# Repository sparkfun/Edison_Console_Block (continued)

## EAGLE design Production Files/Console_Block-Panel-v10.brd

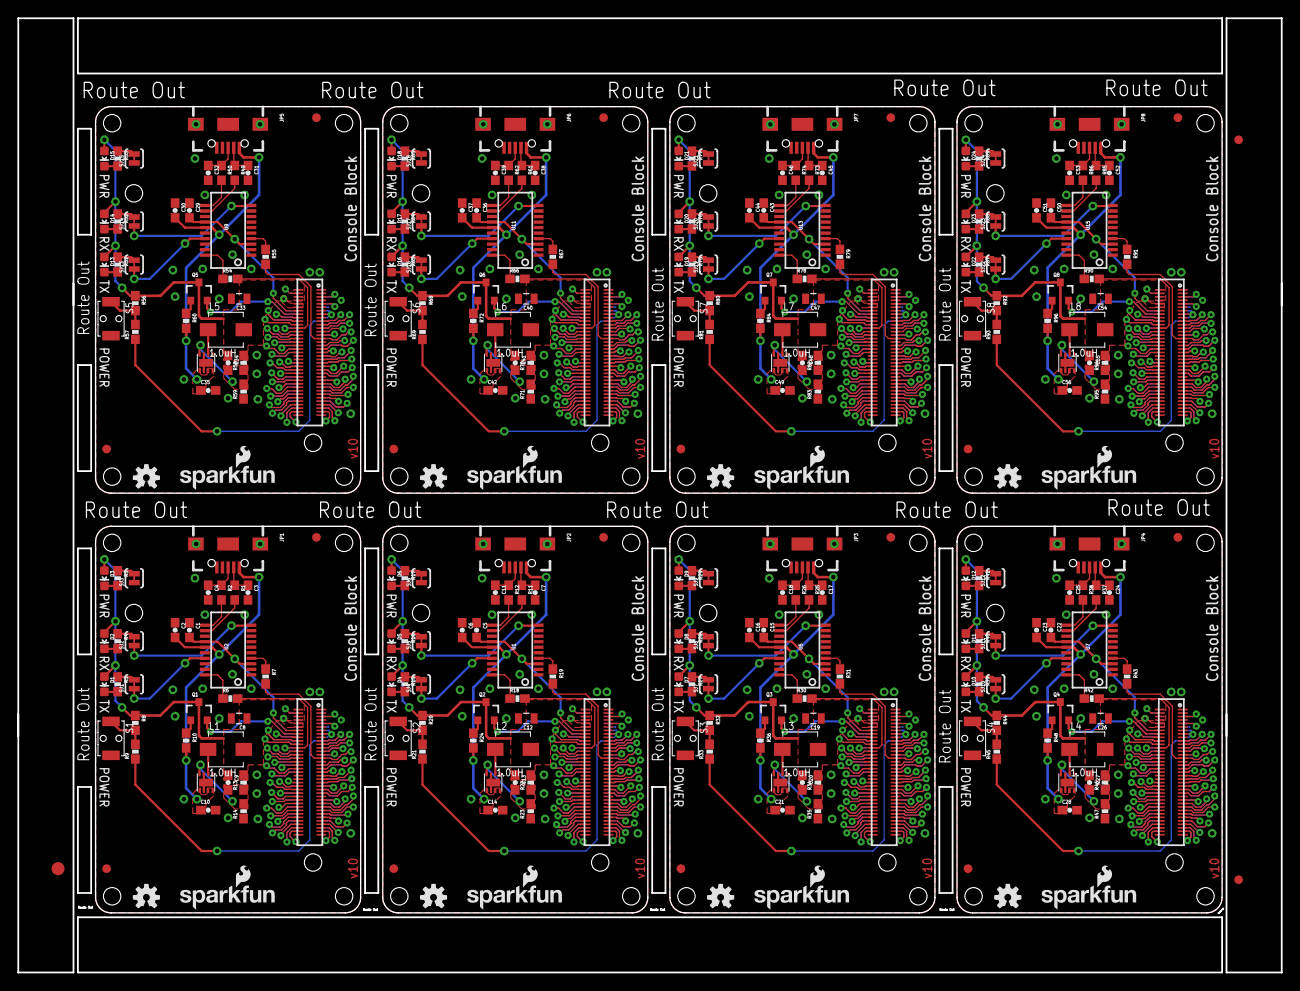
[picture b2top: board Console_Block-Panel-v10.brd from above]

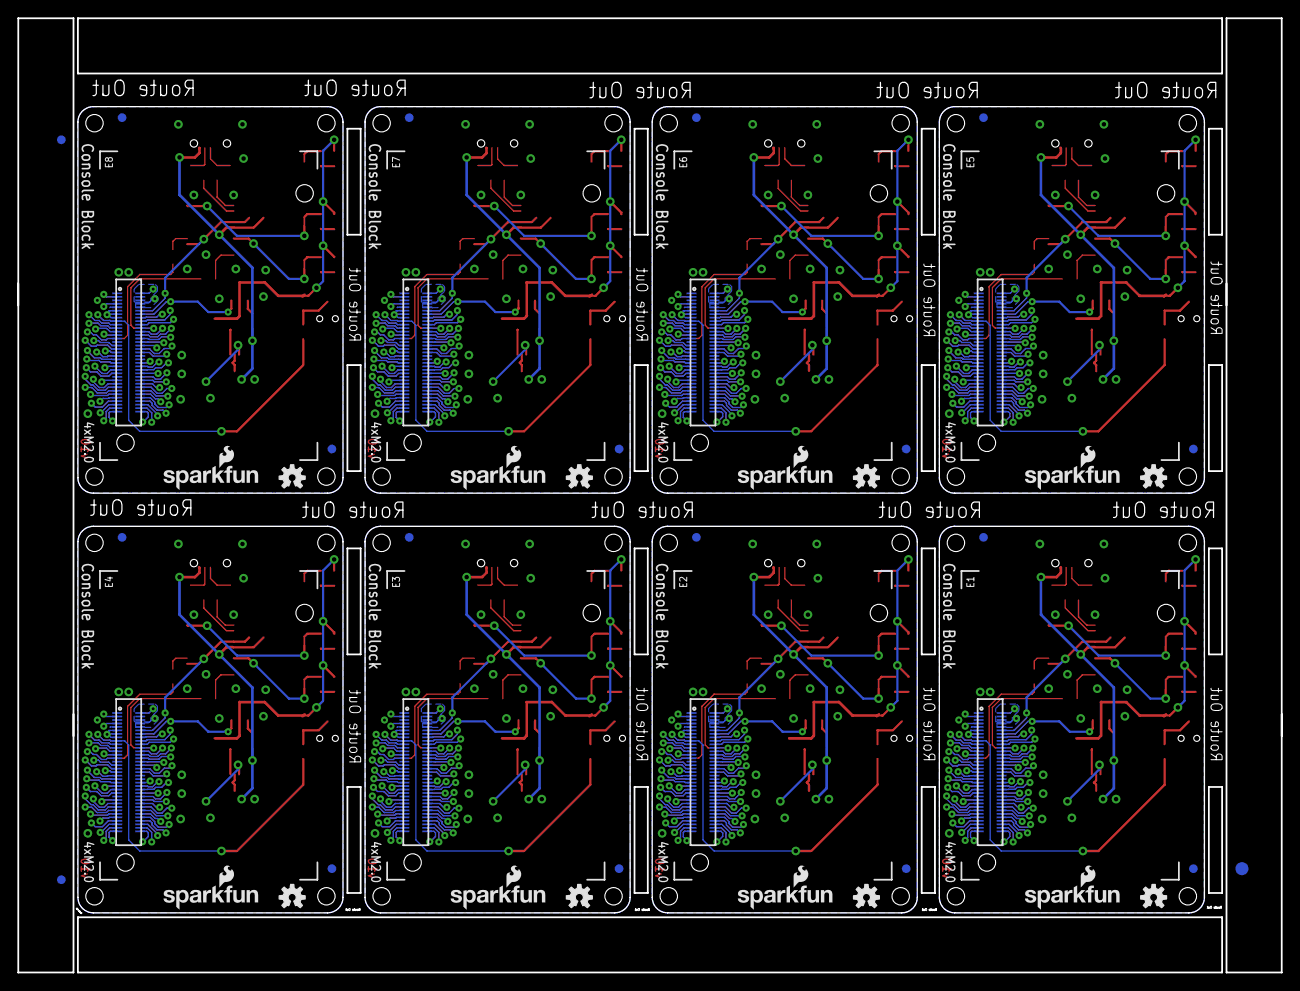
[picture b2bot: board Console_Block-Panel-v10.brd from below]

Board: 2 copper layers, 145.3 x 109.7 mm, 334 parts (51 on the bottom side), 616 nets.

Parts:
C1, C2, C5, C6, C15, C16, C22, C23, C29, C30, C36, C37, C43, C44, C50, C51: 0.1uF; 0603-CAP
C3, C4, C7, C9, C11, C13, C17, C18, C20, C24, C25, C27, C31, C32, C34, C38, C39, C41, C45, C46, C48, C52, C53, C55: 47pF; 0603-CAP
C8, C12, C19, C26, C33, C40, C47, C54: 22uF; 0805
C10, C14, C21, C28, C35, C42, C49, C56: 4.7uF; 0603-CAP
D1, D4, D7, D10, D13, D16, D19, D22: RED; LED-0603
D2, D5, D8, D11, D14, D17, D20, D23: YELLOW; LED-0603
D3, D6, D9, D12, D15, D18, D21, D24: BLUE; LED-0603
E1, E2, E3, E4, E5, E6, E7, E8: EDISON_CONNECTOR_FULLMOUNTING_HOLES; EDISON_DAUGHTER
E$1, E$2: FIDUCIAL-1.5X3
E$3, E$4, E$5, E$6: FIDUCIAL-1X2
FID1, FID2, FID3, FID4, FID5, FID6, FID7, FID8, FID9, FID10, FID11, FID12, FID13, FID14, FID15, FID16, FID17, FID18, FID19, FID20, FID21, FID22, FID23, FID24, FID25, FID26, FID27, FID28, FID29, FID30, FID31, FID32: FIDUCIAL1X2; FIDUCIAL-1X2
JP1, JP2, JP3, JP4, JP5, JP6, JP7, JP8: USB_MICROB; USB-B-MICRO-SMD_V03
L1, L2, L3, L4, L5, L6, L7, L8: 1.0uH; INDUCTOR-SRP4020
LOGO1, LOGO3, LOGO6, LOGO7, LOGO10, LOGO11, LOGO14, LOGO15, LOGO18, LOGO19, LOGO22, LOGO23, LOGO26, LOGO27, LOGO30, LOGO31: SFE_LOGO_NAME_FLAME.1_INCH; SFE_LOGO_NAME_FLAME_.1
LOGO2, LOGO4, LOGO5, LOGO8, LOGO9, LOGO12, LOGO13, LOGO16, LOGO17, LOGO20, LOGO21, LOGO24, LOGO25, LOGO28, LOGO29, LOGO32: OSHW-LOGOS; OSHW-LOGO-S
Q1, Q2, Q3, Q4, Q5, Q6, Q7, Q8: BSS138; SOT23-3
R1, R2, R11, R12, R25, R26, R37, R38, R49, R50, R61, R62, R73, R74, R85, R86: 27; 0603
R3, R4, R5, R10, R15, R16, R17, R24, R27, R28, R29, R36, R39, R40, R41, R48, R51, R52, R53, R60, R63, R64, R65, R72, R75, R76, R77, R84, R87, R88, R89, R96: 1K; 0603-RES
R6, R7, R18, R19, R30, R31, R42, R43, R54, R55, R66, R67, R78, R79, R90, R91: 100; 0603-RES
R8, R20, R32, R44, R56, R68, R80, R92: 10K; 0603-RES
R9, R21, R33, R45, R57, R69, R81, R93: 22; 0603-RES
R13, R22, R34, R46, R58, R70, R82, R94: 680k; 0603-RES
R14, R23, R35, R47, R59, R71, R83, R95: 120k; 0603-RES
S1, S2, S3, S4, S5, S6, S7, S8: POWER; TACTILE_SWITCH-SMD-RIGHT-ANGLE
SJ1, SJ2, SJ3, SJ4, SJ5, SJ6, SJ7, SJ8, SJ9, SJ10, SJ11, SJ12, SJ13, SJ14, SJ15, SJ16, SJ17, SJ18, SJ19, SJ20, SJ21, SJ22, SJ23, SJ24: JUMPER-PAD-2-NC_BY_TRACE; PAD-JUMPER-2-NC_BY_TRACE_YES_SILK
U1, U2, U5, U7, U9, U11, U13, U15: FT231XS-U; SSOP20_L
U3, U4, U6, U8, U10, U12, U14, U16: TPS62065; WSON-8-PAD
U$1, U$2, U$3, U$4, U$5, U$6, U$7, U$8: EDISON_CONNECTOR_FULLHEADER; DF40C-70DP-0.4(51)

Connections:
1.8V: C1.2, E1.12, U2.3, U2.14, U$3.12
1.8V1: C5.2, E2.12, U1.3, U1.14, U$1.12
1.8V2: C15.2, E3.12, U5.3, U5.14, U$2.12
1.8V3: C22.2, E4.12, U7.3, U7.14, U$4.12
1.8V4: C29.2, E5.12, U9.3, U9.14, U$5.12
1.8V5: C36.2, E6.12, U11.3, U11.14, U$6.12
1.8V6: C43.2, E7.12, U13.3, U13.14, U$7.12
1.8V7: C50.2, E8.12, U15.3, U15.14, U$8.12
3.3V: E1.8, E1.10, U$3.8, U$3.10
3.3V1: E2.8, E2.10, U$1.8, U$1.10
3.3V2: E3.8, E3.10, U$2.8, U$2.10
3.3V3: E4.8, E4.10, U$4.8, U$4.10
3.3V4: E5.8, E5.10, U$5.8, U$5.10
3.3V5: E6.8, E6.10, U$6.8, U$6.10
3.3V6: E7.8, E7.10, U$7.8, U$7.10
3.3V7: E8.8, E8.10, U$8.8, U$8.10
5V: C2.2, C10.1, JP1.VBUS1, R10.2, U2.15, U4.5, U4.7, U4.8
5V1: C6.2, C14.1, JP2.VBUS1, R24.2, U1.15, U3.5, U3.7, U3.8
5V2: C16.2, C21.1, JP3.VBUS1, R36.2, U5.15, U6.5, U6.7, U6.8
5V3: C23.2, C28.1, JP4.VBUS1, R48.2, U7.15, U8.5, U8.7, U8.8
5V4: C30.2, C35.1, JP5.VBUS1, R60.2, U9.15, U10.5, U10.7, U10.8
5V5: C37.2, C42.1, JP6.VBUS1, R72.2, U11.15, U12.5, U12.7, U12.8
5V6: C44.2, C49.1, JP7.VBUS1, R84.2, U13.15, U14.5, U14.7, U14.8
5V7: C51.2, C56.1, JP8.VBUS1, R96.2, U15.15, U16.5, U16.7, U16.8
DCIN: E1.14, Q1.2, U$3.14
DCIN1: E2.14, Q2.2, U$1.14
DCIN2: E3.14, Q3.2, U$2.14
DCIN3: E4.14, Q4.2, U$4.14
DCIN4: E5.14, Q5.2, U$5.14
DCIN5: E6.14, Q6.2, U$6.14
DCIN6: E7.14, Q7.2, U$7.14
DCIN7: E8.14, Q8.2, U$8.14
FAULT: E1.19, U$3.19
FAULT1: E2.19, U$1.19
FAULT2: E3.19, U$2.19
FAULT3: E4.19, U$4.19
FAULT4: E5.19, U$5.19
FAULT5: E6.19, U$6.19
FAULT6: E7.19, U$7.19
FAULT7: E8.19, U$8.19
FW_RCVR: E1.69, U$3.69
FW_RCVR1: E2.69, U$1.69
FW_RCVR2: E3.69, U$2.69
FW_RCVR3: E4.69, U$4.69
FW_RCVR4: E5.69, U$5.69
FW_RCVR5: E6.69, U$6.69
FW_RCVR6: E7.69, U$7.69
FW_RCVR7: E8.69, U$8.69
GND: C1.1, C2.1, C3.2, C4.2, C8.2, C10.2, E1.1, E1.5, E1.9, E1.11, E1.13, E1.15, JP1.GND1, JP1.SHIELD1, JP1.SHIELD2, JP1.SHIELD3, R14.1, S1.2, SJ3.1, U2.6, U2.16, U4.1, U4.3, U4.6, U4.PAD, U$3.1, U$3.5, U$3.9, U$3.11, U$3.13, U$3.15
GND1: C5.1, C6.1, C7.2, C11.2, C12.2, C14.2, E2.1, E2.5, E2.9, E2.11, E2.13, E2.15, JP2.GND1, JP2.SHIELD1, JP2.SHIELD2, JP2.SHIELD3, R23.1, S2.2, SJ6.1, U1.6, U1.16, U3.1, U3.3, U3.6, U3.PAD, U$1.1, U$1.5, U$1.9, U$1.11, U$1.13, U$1.15
GND2: C15.1, C16.1, C17.2, C18.2, C19.2, C21.2, E3.1, E3.5, E3.9, E3.11, E3.13, E3.15, JP3.GND1, JP3.SHIELD1, JP3.SHIELD2, JP3.SHIELD3, R35.1, S3.2, SJ9.1, U5.6, U5.16, U6.1, U6.3, U6.6, U6.PAD, U$2.1, U$2.5, U$2.9, U$2.11, U$2.13, U$2.15
GND3: C22.1, C23.1, C24.2, C25.2, C26.2, C28.2, E4.1, E4.5, E4.9, E4.11, E4.13, E4.15, JP4.GND1, JP4.SHIELD1, JP4.SHIELD2, JP4.SHIELD3, R47.1, S4.2, SJ12.1, U7.6, U7.16, U8.1, U8.3, U8.6, U8.PAD, U$4.1, U$4.5, U$4.9, U$4.11, U$4.13, U$4.15
GND4: C29.1, C30.1, C31.2, C32.2, C33.2, C35.2, E5.1, E5.5, E5.9, E5.11, E5.13, E5.15, JP5.GND1, JP5.SHIELD1, JP5.SHIELD2, JP5.SHIELD3, R59.1, S5.2, SJ15.1, U9.6, U9.16, U10.1, U10.3, U10.6, U10.PAD, U$5.1, U$5.5, U$5.9, U$5.11, U$5.13, U$5.15
GND5: C36.1, C37.1, C38.2, C39.2, C40.2, C42.2, E6.1, E6.5, E6.9, E6.11, E6.13, E6.15, JP6.GND1, JP6.SHIELD1, JP6.SHIELD2, JP6.SHIELD3, R71.1, S6.2, SJ18.1, U11.6, U11.16, U12.1, U12.3, U12.6, U12.PAD, U$6.1, U$6.5, U$6.9, U$6.11, U$6.13, U$6.15
GND6: C43.1, C44.1, C45.2, C46.2, C47.2, C49.2, E7.1, E7.5, E7.9, E7.11, E7.13, E7.15, JP7.GND1, JP7.SHIELD1, JP7.SHIELD2, JP7.SHIELD3, R83.1, S7.2, SJ21.1, U13.6, U13.16, U14.1, U14.3, U14.6, U14.PAD, U$7.1, U$7.5, U$7.9, U$7.11, U$7.13, U$7.15
GND7: C50.1, C51.1, C52.2, C53.2, C54.2, C56.2, E8.1, E8.5, E8.9, E8.11, E8.13, E8.15, JP8.GND1, JP8.SHIELD1, JP8.SHIELD2, JP8.SHIELD3, R95.1, S8.2, SJ24.1, U15.6, U15.16, U16.1, U16.3, U16.6, U16.PAD, U$8.1, U$8.5, U$8.9, U$8.11, U$8.13, U$8.15
GP1: E2.48, U$1.48
GP2: E2.42, U$1.42
GP3: E2.34, U$1.34
GP4: E2.32, U$1.32
GP5: E2.30, U$1.30
GP6: E2.28, U$1.28
GP7: E2.26, U$1.26
GP8: E2.25, U$1.25
GP9: E2.24, U$1.24
GP10: E3.48, U$2.48
GP11: E3.42, U$2.42
GP12: E3.34, U$2.34
GP12_PWM0: E1.35, U$3.35
GP12_PWM1: E2.35, U$1.35
GP12_PWM2: E3.35, U$2.35
GP12_PWM3: E4.35, U$4.35
GP12_PWM4: E5.35, U$5.35
GP12_PWM5: E6.35, U$6.35
GP12_PWM6: E7.35, U$7.35
GP12_PWM7: E8.35, U$8.35
GP13: E3.32, U$2.32
GP13_PWM1: E1.33, U$3.33
GP13_PWM2: E2.33, U$1.33
GP13_PWM3: E3.33, U$2.33
GP13_PWM4: E4.33, U$4.33
GP13_PWM5: E5.33, U$5.33
GP13_PWM6: E6.33, U$6.33
GP13_PWM7: E7.33, U$7.33
GP13_PWM8: E8.33, U$8.33
GP14: E1.48, U$3.48
GP15: E1.42, U$3.42
GP16: E3.30, U$2.30
GP17: E3.28, U$2.28
GP18: E3.26, U$2.26
GP19: E3.25, U$2.25
GP19_I2C_1_SCL: E1.41, U$3.41
GP19_I2C_1_SCL1: E2.41, U$1.41
GP19_I2C_1_SCL2: E3.41, U$2.41
GP19_I2C_1_SCL3: E4.41, U$4.41
GP19_I2C_1_SCL4: E5.41, U$5.41
GP19_I2C_1_SCL5: E6.41, U$6.41
GP19_I2C_1_SCL6: E7.41, U$7.41
GP19_I2C_1_SCL7: E8.41, U$8.41
GP20: E3.24, U$2.24
GP20_I2C_1_SDA: E1.43, U$3.43
GP20_I2C_1_SDA1: E2.43, U$1.43
GP20_I2C_1_SDA2: E3.43, U$2.43
GP20_I2C_1_SDA3: E4.43, U$4.43
GP20_I2C_1_SDA4: E5.43, U$5.43
GP20_I2C_1_SDA5: E6.43, U$6.43
GP20_I2C_1_SDA6: E7.43, U$7.43
GP20_I2C_1_SDA7: E8.43, U$8.43
GP21: E4.48, U$4.48
GP22: E4.42, U$4.42
GP23: E4.34, U$4.34
GP24: E4.32, U$4.32
GP25: E4.30, U$4.30
GP26: E4.28, U$4.28
GP27: E4.26, U$4.26
GP27_I2C_6_SCL: E1.45, U$3.45
GP27_I2C_6_SCL1: E2.45, U$1.45
GP27_I2C_6_SCL2: E3.45, U$2.45
GP27_I2C_6_SCL3: E4.45, U$4.45
GP27_I2C_6_SCL4: E5.45, U$5.45
GP27_I2C_6_SCL5: E6.45, U$6.45
GP27_I2C_6_SCL6: E7.45, U$7.45
GP27_I2C_6_SCL7: E8.45, U$8.45
GP28: E4.25, U$4.25
GP28_I2C_6_SDA: E1.47, U$3.47
GP28_I2C_6_SDA1: E2.47, U$1.47
GP28_I2C_6_SDA2: E3.47, U$2.47
GP28_I2C_6_SDA3: E4.47, U$4.47
GP28_I2C_6_SDA4: E5.47, U$5.47
GP28_I2C_6_SDA5: E6.47, U$6.47
GP28_I2C_6_SDA6: E7.47, U$7.47
GP28_I2C_6_SDA7: E8.47, U$8.47
GP29: E4.24, U$4.24
GP30: E5.48, U$5.48
GP31: E5.42, U$5.42
GP32: E5.34, U$5.34
GP33: E5.32, U$5.32
GP34: E5.30, U$5.30
GP35: E5.28, U$5.28
GP36: E5.26, U$5.26
GP37: E5.25, U$5.25
GP38: E5.24, U$5.24
GP39: E6.48, U$6.48
GP40: E6.42, U$6.42
GP40_I2S_2_CLK: E1.52, U$3.52
GP40_I2S_2_CLK1: E2.52, U$1.52
GP40_I2S_2_CLK2: E3.52, U$2.52
GP40_I2S_2_CLK3: E4.52, U$4.52
GP40_I2S_2_CLK4: E5.52, U$5.52
GP40_I2S_2_CLK5: E6.52, U$6.52
GP40_I2S_2_CLK6: E7.52, U$7.52
GP40_I2S_2_CLK7: E8.52, U$8.52
GP41: E6.34, U$6.34
GP41_I2S_2_FS: E1.54, U$3.54
GP41_I2S_2_FS1: E2.54, U$1.54
GP41_I2S_2_FS2: E3.54, U$2.54
GP41_I2S_2_FS3: E4.54, U$4.54
GP41_I2S_2_FS4: E5.54, U$5.54
GP41_I2S_2_FS5: E6.54, U$6.54
GP41_I2S_2_FS6: E7.54, U$7.54
GP41_I2S_2_FS7: E8.54, U$8.54
GP42: E6.32, U$6.32
GP42_I2S_2_RXD: E1.50, U$3.50
GP42_I2S_2_RXD1: E2.50, U$1.50
GP42_I2S_2_RXD2: E3.50, U$2.50
GP42_I2S_2_RXD3: E4.50, U$4.50
GP42_I2S_2_RXD4: E5.50, U$5.50
GP42_I2S_2_RXD5: E6.50, U$6.50
GP42_I2S_2_RXD6: E7.50, U$7.50
GP42_I2S_2_RXD7: E8.50, U$8.50
GP43: E6.30, U$6.30
GP43_I2S_2_TXD: E1.56, U$3.56
GP43_I2S_2_TXD1: E2.56, U$1.56
GP43_I2S_2_TXD2: E3.56, U$2.56
GP43_I2S_2_TXD3: E4.56, U$4.56
GP43_I2S_2_TXD4: E5.56, U$5.56
GP43_I2S_2_TXD5: E6.56, U$6.56
GP43_I2S_2_TXD6: E7.56, U$7.56
GP43_I2S_2_TXD7: E8.56, U$8.56
GP44: E1.24, U$3.24
GP45: E1.26, U$3.26
GP46: E1.28, U$3.28
GP47: E1.30, U$3.30
GP48: E1.32, U$3.32
GP49: E1.34, U$3.34
GP50: E6.28, U$6.28
GP51: E6.26, U$6.26
GP52: E6.25, U$6.25
GP53: E6.24, U$6.24
GP54: E7.48, U$7.48
GP55: E7.42, U$7.42
GP56: E7.34, U$7.34
GP57: E7.32, U$7.32
GP58: E7.30, U$7.30
GP59: E7.28, U$7.28
GP60: E7.26, U$7.26
GP61: E7.25, U$7.25
GP62: E7.24, U$7.24
GP63: E8.48, U$8.48
GP64: E8.42, U$8.42
GP65: E8.34, U$8.34
GP66: E8.32, U$8.32
GP67: E8.30, U$8.30
GP68: E8.28, U$8.28
GP69: E8.26, U$8.26
GP70: E8.25, U$8.25
GP71: E8.24, U$8.24
GP77_SD_0_CD#: E1.60, U$3.60
GP77_SD_0_CD#1: E2.60, U$1.60
GP77_SD_0_CD#2: E3.60, U$2.60
GP77_SD_0_CD#3: E4.60, U$4.60
GP77_SD_0_CD#4: E5.60, U$5.60
GP77_SD_0_CD#5: E6.60, U$6.60
GP77_SD_0_CD#6: E7.60, U$7.60
GP77_SD_0_CD#7: E8.60, U$8.60
GP78_SD_0_CLK: E1.58, U$3.58
GP78_SD_0_CLK1: E2.58, U$1.58
GP78_SD_0_CLK2: E3.58, U$2.58
GP78_SD_0_CLK3: E4.58, U$4.58
GP78_SD_0_CLK4: E5.58, U$5.58
GP78_SD_0_CLK5: E6.58, U$6.58
GP78_SD_0_CLK6: E7.58, U$7.58
GP78_SD_0_CLK7: E8.58, U$8.58
GP79_SD_0_CMD: E1.62, U$3.62
GP79_SD_0_CMD1: E2.62, U$1.62
GP79_SD_0_CMD2: E3.62, U$2.62
GP79_SD_0_CMD3: E4.62, U$4.62
GP79_SD_0_CMD4: E5.62, U$5.62
GP79_SD_0_CMD5: E6.62, U$6.62
GP79_SD_0_CMD6: E7.62, U$7.62
GP79_SD_0_CMD7: E8.62, U$8.62
GP80_SD_0_DAT0: E1.66, U$3.66
GP80_SD_0_DAT1: E2.66, U$1.66
GP80_SD_0_DAT2: E3.66, U$2.66
GP80_SD_0_DAT3: E4.66, U$4.66
GP80_SD_0_DAT4: E5.66, U$5.66
GP80_SD_0_DAT5: E6.66, U$6.66
GP80_SD_0_DAT6: E7.66, U$7.66
GP80_SD_0_DAT7: E8.66, U$8.66
GP81_SD_0_DAT1: E1.70, U$3.70
GP81_SD_0_DAT2: E2.70, U$1.70
GP81_SD_0_DAT3: E3.70, U$2.70
GP81_SD_0_DAT4: E4.70, U$4.70
GP81_SD_0_DAT5: E5.70, U$5.70
GP81_SD_0_DAT6: E6.70, U$6.70
GP81_SD_0_DAT7: E7.70, U$7.70
GP81_SD_0_DAT8: E8.70, U$8.70
GP82_SD_0_DAT1: E2.64, U$1.64
GP82_SD_0_DAT2: E1.64, U$3.64
GP82_SD_0_DAT3: E3.64, U$2.64
GP82_SD_0_DAT4: E4.64, U$4.64
GP82_SD_0_DAT5: E5.64, U$5.64
GP82_SD_0_DAT6: E6.64, U$6.64
GP82_SD_0_DAT7: E7.64, U$7.64
GP82_SD_0_DAT8: E8.64, U$8.64
GP83_SD_0_DAT1: E2.68, U$1.68
GP83_SD_0_DAT2: E3.68, U$2.68
GP83_SD_0_DAT3: E1.68, U$3.68
GP83_SD_0_DAT4: E4.68, U$4.68
GP83_SD_0_DAT5: E5.68, U$5.68
GP83_SD_0_DAT6: E6.68, U$6.68
GP83_SD_0_DAT7: E7.68, U$7.68
GP83_SD_0_DAT8: E8.68, U$8.68
GP84_SD_CLK_FB: E1.44, U$3.44
GP84_SD_CLK_FB1: E2.44, U$1.44
GP84_SD_CLK_FB2: E3.44, U$2.44
GP84_SD_CLK_FB3: E4.44, U$4.44
GP84_SD_CLK_FB4: E5.44, U$5.44
GP84_SD_CLK_FB5: E6.44, U$6.44
GP84_SD_CLK_FB6: E7.44, U$7.44
GP84_SD_CLK_FB7: E8.44, U$8.44
GP109_SPI_2_CLK: E1.55, U$3.55
GP109_SPI_2_CLK1: E2.55, U$1.55
GP109_SPI_2_CLK2: E3.55, U$2.55
GP109_SPI_2_CLK3: E4.55, U$4.55
GP109_SPI_2_CLK4: E5.55, U$5.55
GP109_SPI_2_CLK5: E6.55, U$6.55
GP109_SPI_2_CLK6: E7.55, U$7.55
GP109_SPI_2_CLK7: E8.55, U$8.55
GP110_SPI_2_FS0: E1.53, U$3.53
GP110_SPI_2_FS1: E2.53, U$1.53
GP110_SPI_2_FS2: E3.53, U$2.53
GP110_SPI_2_FS3: E4.53, U$4.53
GP110_SPI_2_FS4: E5.53, U$5.53
GP110_SPI_2_FS5: E6.53, U$6.53
GP110_SPI_2_FS6: E7.53, U$7.53
GP110_SPI_2_FS7: E8.53, U$8.53
GP111_SPI_2_FS1: E1.51, U$3.51
GP111_SPI_2_FS2: E2.51, U$1.51
GP111_SPI_2_FS3: E3.51, U$2.51
GP111_SPI_2_FS4: E4.51, U$4.51
GP111_SPI_2_FS5: E5.51, U$5.51
GP111_SPI_2_FS6: E6.51, U$6.51
GP111_SPI_2_FS7: E7.51, U$7.51
GP111_SPI_2_FS8: E8.51, U$8.51
GP114_SPI_2_RXD: E1.59, U$3.59
GP114_SPI_2_RXD1: E2.59, U$1.59
GP114_SPI_2_RXD2: E3.59, U$2.59
GP114_SPI_2_RXD3: E4.59, U$4.59
GP114_SPI_2_RXD4: E5.59, U$5.59
GP114_SPI_2_RXD5: E6.59, U$6.59
GP114_SPI_2_RXD6: E7.59, U$7.59
GP114_SPI_2_RXD7: E8.59, U$8.59
GP115_SPI_2_TXD: E1.57, U$3.57
GP115_SPI_2_TXD1: E2.57, U$1.57
GP115_SPI_2_TXD2: E3.57, U$2.57
GP115_SPI_2_TXD3: E4.57, U$4.57
GP115_SPI_2_TXD4: E5.57, U$5.57
GP115_SPI_2_TXD5: E6.57, U$6.57
GP115_SPI_2_TXD6: E7.57, U$7.57
GP115_SPI_2_TXD7: E8.57, U$8.57
GP128_UART_1_CTS: E1.65, U$3.65
GP128_UART_1_CTS1: E2.65, U$1.65
GP128_UART_1_CTS2: E3.65, U$2.65
GP128_UART_1_CTS3: E4.65, U$4.65
GP128_UART_1_CTS4: E5.65, U$5.65
GP128_UART_1_CTS5: E6.65, U$6.65
GP128_UART_1_CTS6: E7.65, U$7.65
GP128_UART_1_CTS7: E8.65, U$8.65
GP129_UART_1_RTS: E1.63, U$3.63
GP129_UART_1_RTS1: E2.63, U$1.63
GP129_UART_1_RTS2: E3.63, U$2.63
GP129_UART_1_RTS3: E4.63, U$4.63
GP129_UART_1_RTS4: E5.63, U$5.63
GP129_UART_1_RTS5: E6.63, U$6.63
GP129_UART_1_RTS6: E7.63, U$7.63
GP129_UART_1_RTS7: E8.63, U$8.63
GP130_UART_1_RX: E1.61, U$3.61
GP130_UART_1_RX1: E2.61, U$1.61
GP130_UART_1_RX2: E3.61, U$2.61
GP130_UART_1_RX3: E4.61, U$4.61
GP130_UART_1_RX4: E5.61, U$5.61
GP130_UART_1_RX5: E6.61, U$6.61
GP130_UART_1_RX6: E7.61, U$7.61
GP130_UART_1_RX7: E8.61, U$8.61
GP131_UART_1_TX: E1.46, U$3.46
GP131_UART_1_TX1: E2.46, U$1.46
GP131_UART_1_TX2: E3.46, U$2.46
GP131_UART_1_TX3: E4.46, U$4.46
GP131_UART_1_TX4: E5.46, U$5.46
GP131_UART_1_TX5: E6.46, U$6.46
GP131_UART_1_TX6: E7.46, U$7.46
GP131_UART_1_TX7: E8.46, U$8.46
GP134_UART_2_RX: E1.22, R6.2, U$3.22
GP134_UART_2_RX1: E2.22, R18.2, U$1.22
GP134_UART_2_RX2: E3.22, R30.2, U$2.22
GP134_UART_2_RX3: E4.22, R42.2, U$4.22
GP134_UART_2_RX4: E5.22, R54.2, U$5.22
GP134_UART_2_RX5: E6.22, R66.2, U$6.22
GP134_UART_2_RX6: E7.22, R78.2, U$7.22
GP134_UART_2_RX7: E8.22, R90.2, U$8.22
GP135_UART_2_TX: E1.27, R7.2, U$3.27
GP135_UART_2_TX1: E2.27, R19.2, U$1.27
GP135_UART_2_TX2: E3.27, R31.2, U$2.27
GP135_UART_2_TX3: E4.27, R43.2, U$4.27
GP135_UART_2_TX4: E5.27, R55.2, U$5.27
GP135_UART_2_TX5: E6.27, R67.2, U$6.27
GP135_UART_2_TX6: E7.27, R79.2, U$7.27
GP135_UART_2_TX7: E8.27, R91.2, U$8.27
GP165: E1.25, U$3.25
GP182_PWM1: E2.37, U$1.37
GP182_PWM2: E1.37, U$3.37
GP182_PWM3: E3.37, U$2.37
GP182_PWM4: E4.37, U$4.37
GP182_PWM5: E5.37, U$5.37
GP182_PWM6: E6.37, U$6.37
GP182_PWM7: E7.37, U$7.37
GP182_PWM8: E8.37, U$8.37
GP183_PWM1: E2.39, U$1.39
GP183_PWM2: E3.39, U$2.39
GP183_PWM3: E1.39, U$3.39
GP183_PWM4: E4.39, U$4.39
GP183_PWM5: E5.39, U$5.39
GP183_PWM6: E6.39, U$6.39
GP183_PWM7: E7.39, U$7.39
GP183_PWM8: E8.39, U$8.39
MSIC_SLP_CLK: E1.7, U$3.7
MSIC_SLP_CLK1: E2.7, U$1.7
MSIC_SLP_CLK2: E3.7, U$2.7
MSIC_SLP_CLK3: E4.7, U$4.7
MSIC_SLP_CLK4: E5.7, U$5.7
MSIC_SLP_CLK5: E6.7, U$6.7
MSIC_SLP_CLK6: E7.7, U$7.7
MSIC_SLP_CLK7: E8.7, U$8.7
unnamed: SJ1.1, U2.17
unnamed: C3.1, JP1.D-1, R1.1
unnamed: C4.1, JP1.D+1, R2.1
unnamed: R1.2, U2.12
unnamed: R2.2, U2.11
unnamed: SJ2.1, U2.10
unnamed: R3.1, SJ1.2
unnamed: R4.1, SJ2.2
unnamed: D1.C, R3.2
unnamed: D2.C, R4.2
unnamed: R6.1, U2.20
unnamed: D3.C, R5.2
unnamed: R5.1, SJ3.2
unnamed: R7.1, U2.4
unnamed: R8.2, R9.2, S1.1
unnamed: Q1.1, R10.1
unnamed: C7.1, JP2.D-1, R11.1
unnamed: C9.2, R13.1, R14.2, U4.4
unnamed: L1.P$1, U4.2
unnamed: C11.1, JP2.D+1, R12.1
unnamed: R11.2, U1.12
unnamed: R12.2, U1.11
unnamed: SJ4.1, U1.17
unnamed: SJ5.1, U1.10
unnamed: R15.1, SJ4.2
unnamed: R16.1, SJ5.2
unnamed: D4.C, R15.2
unnamed: D5.C, R16.2
unnamed: D6.C, R17.2
unnamed: R17.1, SJ6.2
unnamed: R18.1, U1.20
unnamed: R19.1, U1.4
unnamed: R20.2, R21.2, S2.1
unnamed: C13.2, R22.1, R23.2, U3.4
unnamed: L2.P$1, U3.2
unnamed: Q2.1, R24.1
unnamed: C17.1, JP3.D-1, R25.1
unnamed: C18.1, JP3.D+1, R26.1
unnamed: R25.2, U5.12
unnamed: R26.2, U5.11
unnamed: SJ7.1, U5.17
unnamed: SJ8.1, U5.10
unnamed: R27.1, SJ7.2
unnamed: R28.1, SJ8.2
unnamed: D7.C, R27.2
unnamed: D8.C, R28.2
unnamed: D9.C, R29.2
unnamed: R29.1, SJ9.2
unnamed: R30.1, U5.20
unnamed: R31.1, U5.4
unnamed: R32.2, R33.2, S3.1
unnamed: C20.2, R34.1, R35.2, U6.4
unnamed: L3.P$1, U6.2
unnamed: Q3.1, R36.1
unnamed: C24.1, JP4.D-1, R37.1
unnamed: C25.1, JP4.D+1, R38.1
unnamed: R37.2, U7.12
unnamed: R38.2, U7.11
unnamed: SJ10.1, U7.17
unnamed: SJ11.1, U7.10
unnamed: R39.1, SJ10.2
unnamed: R40.1, SJ11.2
unnamed: D10.C, R39.2
unnamed: D11.C, R40.2
unnamed: D12.C, R41.2
unnamed: R41.1, SJ12.2
unnamed: R42.1, U7.20
unnamed: R43.1, U7.4
unnamed: R44.2, R45.2, S4.1
unnamed: C27.2, R46.1, R47.2, U8.4
unnamed: L4.P$1, U8.2
unnamed: Q4.1, R48.1
unnamed: C31.1, JP5.D-1, R49.1
unnamed: C32.1, JP5.D+1, R50.1
unnamed: R49.2, U9.12
unnamed: R50.2, U9.11
unnamed: SJ13.1, U9.17
unnamed: SJ14.1, U9.10
unnamed: R51.1, SJ13.2
unnamed: R52.1, SJ14.2
unnamed: D13.C, R51.2
unnamed: D14.C, R52.2
unnamed: D15.C, R53.2
unnamed: R53.1, SJ15.2
unnamed: R54.1, U9.20
unnamed: R55.1, U9.4
unnamed: R56.2, R57.2, S5.1
unnamed: C34.2, R58.1, R59.2, U10.4
unnamed: L5.P$1, U10.2
unnamed: Q5.1, R60.1
unnamed: C38.1, JP6.D-1, R61.1
unnamed: C39.1, JP6.D+1, R62.1
unnamed: R61.2, U11.12
unnamed: R62.2, U11.11
unnamed: SJ16.1, U11.17
unnamed: SJ17.1, U11.10
unnamed: R63.1, SJ16.2
unnamed: R64.1, SJ17.2
unnamed: D16.C, R63.2
unnamed: D17.C, R64.2
unnamed: D18.C, R65.2
unnamed: R65.1, SJ18.2
unnamed: R66.1, U11.20
unnamed: R67.1, U11.4
unnamed: R68.2, R69.2, S6.1
unnamed: C41.2, R70.1, R71.2, U12.4
unnamed: L6.P$1, U12.2
unnamed: Q6.1, R72.1
unnamed: C45.1, JP7.D-1, R73.1
unnamed: C46.1, JP7.D+1, R74.1
unnamed: R73.2, U13.12
unnamed: R74.2, U13.11
unnamed: SJ19.1, U13.17
unnamed: SJ20.1, U13.10
unnamed: R75.1, SJ19.2
unnamed: R76.1, SJ20.2
unnamed: D19.C, R75.2
unnamed: D20.C, R76.2
unnamed: D21.C, R77.2
unnamed: R77.1, SJ21.2
unnamed: R78.1, U13.20
unnamed: R79.1, U13.4
unnamed: R80.2, R81.2, S7.1
unnamed: C48.2, R82.1, R83.2, U14.4
unnamed: L7.P$1, U14.2
unnamed: Q7.1, R84.1
unnamed: C52.1, JP8.D-1, R85.1
unnamed: C53.1, JP8.D+1, R86.1
unnamed: R85.2, U15.12
unnamed: R86.2, U15.11
unnamed: SJ22.1, U15.17
unnamed: SJ23.1, U15.10
unnamed: R87.1, SJ22.2
unnamed: R88.1, SJ23.2
unnamed: D22.C, R87.2
unnamed: D23.C, R88.2
unnamed: D24.C, R89.2
unnamed: R89.1, SJ24.2
unnamed: R90.1, U15.20
unnamed: R91.1, U15.4
unnamed: R92.2, R93.2, S8.1
unnamed: C55.2, R94.1, R95.2, U16.4
unnamed: L8.P$1, U16.2
unnamed: Q8.1, R96.1
OSC_CLK_OUT: E1.67, U$3.67
OSC_CLK_OUT1: E2.67, U$1.67
OSC_CLK_OUT2: E3.67, U$2.67
OSC_CLK_OUT3: E4.67, U$4.67
OSC_CLK_OUT4: E5.67, U$5.67
OSC_CLK_OUT5: E6.67, U$6.67
OSC_CLK_OUT6: E7.67, U$7.67
OSC_CLK_OUT7: E8.67, U$8.67
PSW: E1.21, U$3.21
PSW1: E2.21, U$1.21
PSW2: E3.21, U$2.21
PSW3: E4.21, U$4.21
PSW4: E5.21, U$5.21
PSW5: E6.21, U$6.21
PSW6: E7.21, U$7.21
PSW7: E8.21, U$8.21
PWRBTN#: E1.17, R9.1, U$3.17
PWRBTN#1: E2.17, R21.1, U$1.17
PWRBTN#2: E3.17, R33.1, U$2.17
PWRBTN#3: E4.17, R45.1, U$4.17
PWRBTN#4: E5.17, R57.1, U$5.17
PWRBTN#5: E6.17, R69.1, U$6.17
PWRBTN#6: E7.17, R81.1, U$7.17
PWRBTN#7: E8.17, R93.1, U$8.17
RCVR_MODE: E1.31, U$3.31
RCVR_MODE1: E2.31, U$1.31
RCVR_MODE2: E3.31, U$2.31
RCVR_MODE3: E4.31, U$4.31
RCVR_MODE4: E5.31, U$5.31
RCVR_MODE5: E6.31, U$6.31
RCVR_MODE6: E7.31, U$7.31
RCVR_MODE7: E8.31, U$8.31
RESET_OUT#: E1.36, U$3.36
RESET_OUT#1: E2.36, U$1.36
RESET_OUT#2: E3.36, U$2.36
RESET_OUT#3: E4.36, U$4.36
RESET_OUT#4: E5.36, U$5.36
RESET_OUT#5: E6.36, U$6.36
RESET_OUT#6: E7.36, U$7.36
RESET_OUT#7: E8.36, U$8.36
USB_DN: E1.18, U$3.18
USB_DN1: E2.18, U$1.18
USB_DN2: E3.18, U$2.18
USB_DN3: E4.18, U$4.18
USB_DN4: E5.18, U$5.18
USB_DN5: E6.18, U$6.18
USB_DN6: E7.18, U$7.18
USB_DN7: E8.18, U$8.18
USB_DP: E1.16, U$3.16
USB_DP1: E2.16, U$1.16
USB_DP2: E3.16, U$2.16
USB_DP3: E4.16, U$4.16
USB_DP4: E5.16, U$5.16
USB_DP5: E6.16, U$6.16
USB_DP6: E7.16, U$7.16
USB_DP7: E8.16, U$8.16
USB_ID: E1.3, U$3.3
USB_ID1: E2.3, U$1.3
USB_ID2: E3.3, U$2.3
USB_ID3: E4.3, U$4.3
USB_ID4: E5.3, U$5.3
USB_ID5: E6.3, U$6.3
USB_ID6: E7.3, U$7.3
USB_ID7: E8.3, U$8.3
USB_VBUS: E1.20, U$3.20
USB_VBUS1: E2.20, U$1.20
USB_VBUS2: E3.20, U$2.20
USB_VBUS3: E4.20, U$4.20
USB_VBUS4: E5.20, U$5.20
USB_VBUS5: E6.20, U$6.20
USB_VBUS6: E7.20, U$7.20
USB_VBUS7: E8.20, U$8.20
VSYS: C8.1, C9.1, D1.A, D2.A, D3.A, E1.2, E1.4, E1.6, L1.P$2, Q1.3, R8.1, R13.2, U$3.2, U$3.4, U$3.6
VSYS1: C12.1, C13.1, D4.A, D5.A, D6.A, E2.2, E2.4, E2.6, L2.P$2, Q2.3, R20.1, R22.2, U$1.2, U$1.4, U$1.6
VSYS2: C19.1, C20.1, D7.A, D8.A, D9.A, E3.2, E3.4, E3.6, L3.P$2, Q3.3, R32.1, R34.2, U$2.2, U$2.4, U$2.6
VSYS3: C26.1, C27.1, D10.A, D11.A, D12.A, E4.2, E4.4, E4.6, L4.P$2, Q4.3, R44.1, R46.2, U$4.2, U$4.4, U$4.6
VSYS4: C33.1, C34.1, D13.A, D14.A, D15.A, E5.2, E5.4, E5.6, L5.P$2, Q5.3, R56.1, R58.2, U$5.2, U$5.4, U$5.6
VSYS5: C40.1, C41.1, D16.A, D17.A, D18.A, E6.2, E6.4, E6.6, L6.P$2, Q6.3, R68.1, R70.2, U$6.2, U$6.4, U$6.6
VSYS6: C47.1, C48.1, D19.A, D20.A, D21.A, E7.2, E7.4, E7.6, L7.P$2, Q7.3, R80.1, R82.2, U$7.2, U$7.4, U$7.6
VSYS7: C54.1, C55.1, D22.A, D23.A, D24.A, E8.2, E8.4, E8.6, L8.P$2, Q8.3, R92.1, R94.2, U$8.2, U$8.4, U$8.6
V_BAT_BKUP: E1.23, U$3.23
V_BAT_BKUP1: E2.23, U$1.23
V_BAT_BKUP2: E3.23, U$2.23
V_BAT_BKUP3: E4.23, U$4.23
V_BAT_BKUP4: E5.23, U$5.23
V_BAT_BKUP5: E6.23, U$6.23
V_BAT_BKUP6: E7.23, U$7.23
V_BAT_BKUP7: E8.23, U$8.23
